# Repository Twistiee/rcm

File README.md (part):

# RCM — Relay Control Module

A CAN-controlled relay driver for a car. **21 universal channels**, each of which is
simultaneously a low-side output *and* an input — so the same board builds as a relay
controller or as a switch panel, decided in firmware rather than by a different PCB.

Designed for a [rusEFI](https://rusefi.com/) bus (uaEFI SUPER ECU + uaDASH display), but
nothing about it is rusEFI-specific beyond the choice of message IDs.

> ### A note on how this was built
>
> **This project is largely AI-developed.** The schematic, PCB layout, firmware and
> documentation were written by me working with Claude, and much of the text and code here
> came out of that. It is called out up front because some people would rather know, and
> because it should colour how much you trust it.
>
> What it does *not* mean is unreviewed or untested. The board exists and has been brought
> up on the bench; the claims in the Status section below were measured rather than
> asserted, and where something has only been reasoned about it says so. The firmware has a
> host-side unit test suite. Bring-up still found real bugs that review had missed — which
> is rather the point of the Status section.
>
> Treat it as you would any one-person hobby project: read the schematic before you build
> it, and don't put it in charge of anything you can't afford to have fail.

---

## Status — read this first

**revA has been built, powered and brought up.** Every subsystem has run on real
hardware: the MCU and its 8 MHz crystal (in use only since 2026-10-26 -- see "The core
runs from the crystal" in `firmware/README.md`), USB, the DIP straps, the EEPROM, CAN through the
transceiver onto a real bus, the IMU, the 12 V sense, the self-latching power, the
watchdog, the output drivers under a real relay load, a stored configuration surviving a
full save-reset-read cycle, and the board switching itself off. 289 host unit tests pass
alongside that.

What that does **not** mean is that it is proven in a car. Specifically, still untested:

- **board-to-board peer mirroring** — the keypad role strap is proven and a board does
  come up as a keypad, but only one board has ever been powered, so the peer link has been
  exercised only with a PC pretending to be the other board
- **more than two channels under load at once**, and nothing thermal

One genuine hardware flaw has been found, and it is a missing capability rather than a
functional fault: **revA cannot reach USB DFU.** `BOOT1` is `PB2`, which this board uses
for `SR_OE_N` and holds high at reset, so lifting BOOT0 boots from SRAM instead of the ROM
bootloader. The `J_BOOT` header is fitted and works; the pin conflict defeats it. Firmware
therefore needs an ST-Link on `J_SWD`. Configuration is unaffected — that is all over CAN.
`DESIGN.md` has the analysis and the one-net revB fix.

Bring-up found three real firmware bugs that no amount of desk testing had: a `%f` in
printf corrupting memory, a strap display that could never show a change, and a short
press on the ignition button switching the board back off. `DESIGN.md` records those and
everything else found along the way, which is a fair guide to how much is probably left.

### What happens when it resets

This is a PDM. Running a main relay, a fuel pump and an injector feed is the job, not an
edge case. But there is one behaviour to design around:

**On any reset, `R_OE` parks all 21 channels high-impedance until firmware re-enables
them.** Every channel drops. The firmware adopts `failsafe_state` and goes live as its
first act, and on revA hardware that is **22 ms**, measured by the self-test build's `W`
command rather than estimated. Add a few ms of pre-`main()` crystal and PLL startup that
`millis()` cannot see, so call it **~25 ms**. That applies equally to a cold start and to
a watchdog reset, so a main relay behind this board closes with the key rather than after
a timeout.

Most of the 22 ms is the EEPROM: the board cannot apply `failsafe_state` before it has
read `failsafe_state`, so `cfg_load()` is unavoidably inside the dropout. A scope on any
channel gives the true figure including pre-`main()` time.

So the question for each load is not "is this engine-critical" but **"what does 25 ms off
do to it?"**

| Load | 25 ms off | Verdict |
|---|---|---|
| Fan, fuel pump, lights, horn, accessories | invisible | fine |
| Injector / coil supply via a main relay | at worst a single missed event | **fine — set `failsafe_state` to hold it on** |
| **ECU power itself** | the ECU reboots, which really is a stall | **give the ECU its own ignition-switched feed** |
| **Brake lights** | harmless in itself | **hardwire anyway** — see below |

**`failsafe_state` is the board's resting state**, not just a bus-timeout behaviour: it is
what gets applied at power-up, after a watchdog reset, and whenever the bus goes quiet —
anything a CAN command has not overridden. It defaults to all-off, which is right for
lighting and wrong for anything that should be on by default. It is per-channel, so one
board can drop its lighting and hold its engine loads. Set it deliberately.

**Brake lights are a different argument.** Not dropout time — a hardwired brake switch is
simply simpler and more reliable than anything running on a microcontroller, and there is
no upside to inserting one. Wire the switch straight through, and tap the switched feed
into a spare channel set to `CH_INPUT` if you want the board to know about it. 1.2 mA, and
it cannot affect the lamps.

Roadworthiness and legal compliance of anything you build with this are yours.

---

## What it does

| | |
|---|---|
| **Channels** | 21, low-side switched, 7 per driver |
| **Drivers** | 3 × TPL7407L (MOSFET, not Darlington — see below) |
| **I/O expansion** | 74HC595 out / 74HC165 in, daisy-chained |
| **MCU** | STM32F446RET6, LQFP-64 |
| **Bus** | CAN, switchable termination, any exact bitrate |
| **Sensing** | every channel is read back continuously, including while driving |
| **IMU** | Bosch BMI270, 6-axis |
| **Board** | 140 × 70 mm, 4-layer, solid ground plane |

## Ratings

| | |
|---|---|
| Supply | 7–30 V (12 V nominal); board draws ~100 mA |
| **Per channel, one or two on** | **600 mA** sink, 30 V max |
| **Per channel, all 7 of a tile on** | **~250 mA** — limited by the driver package, not the silicon |
| All 21 channels | ~3.5 A total with typical 85 Ω relay coils |
| Ground return | **all channels share one pole on `J_PWR`**, ~8 A |
| Ambient | −20 to +70 °C |

The channels **switch relay coils, they do not carry load current** — that is the whole
architecture. `DESIGN.md` has the worked numbers, including why 600 mA is not an all-on
figure.

## The channel trick

Each channel's terminal connects to three things at once — a driver output, a permanently
connected 1M/270k sense divider, and a fitted 10k pull-down:

- **As an output** it sinks a relay coil to ground.
- **As an input** a button wired to +12V pulls it high; the pull-down gives 1.2mA of wetting
  current, enough to keep switch contacts from going oxide-flaky.
- **As a diagnostic**, because the divider never disconnects, an idle channel reads battery
  voltage through a healthy relay coil and 0V through a blown fuse. **Fuse detection falls
  out of the same wiring** — no extra parts.

Getting all three from one resistor took a few goes. A pull-*up* would have been the obvious
choice and it silently breaks fuse sensing: blown and healthy both read high, 20mV apart.

The same pull-down has a sting worth knowing: an un-driven channel is **not open**, it is
10k to ground, and it will pass ~1mA from anything pulled up to 12V. Relay coils ignore
that. Optocouplers and MOSFET gates do not — so a generic "active low" relay module wired
straight to a channel sits with its relays energised. `DESIGN.md` has the fix.

## Configuration

An 8-way DIP sets what can't be fixed over the bus once it's wrong:

| Pos | Function |
|---|---|
| 1 | CAN termination (passive, parallels a solder jumper) |
| 2 | Role — relay module or keypad |
| 3–4 | Node address |
| 5 | CAN bitrate — forces 500k, for when you configure yourself off the bus |
| 6 | Publish IMU data — only one board per car should |

Four relay modules and four keypads can share a bus. Everything else — channel modes,
bitrate, message IDs, failsafe states — lives in EEPROM and is changeable over CAN.

## Firmware

PlatformIO + STM32duino, in [`firmware/`](firmware/) — see
[`firmware/README.md`](firmware/README.md) for the detail.

- 21 channels, in or out per channel as a **software** table, changeable over CAN
- **Coil-circuit diagnosis** — blown fuse, missing relay, open coil or broken wire, all
  reported per channel, and a short-to-12V too
- **Input behaviours**: momentary, **toggle** (a momentary button driving a latching
  load), and **hold-to-arm** (true only once held, for things a knock must not arm)
- **Output behaviours**: steady, flash on a shared period so several channels stay in
  phase, single pulse, and delay-off
- CAN at **500 kbps by default and any exact bitrate you like**. Bit timing is solved at
  runtime for an 87.5% sample point; if a rate cannot be produced exactly, it refuses to
  start rather than running the bus 1% out
- Node addressing for 8 boards, CAN-loss failsafe, ignition-off shutdown, watchdog
- **Everything is configurable over CAN, and readable back over CAN** — every setting has
  a getter as well as a setter, so a tool can ask a board what it is rather than infer it
- Optional **keypad → relay peer mirroring**, so a button panel can drive a relay module
  with no ECU in the middle

```
pio run -d firmware                     build
pio run -d firmware -e selftest -t upload   bring-up console over USB-C
pio test -d firmware -e native          289 host unit tests
```

**Two bring-up paths.** A **USB-C console** needs nothing but the cable — it proves the
DIP, the EEPROM, the CAN controller via internal loopback, the IMU, and walks all 21
channels. A **PC-side CAN tool** (`firmware/tools/rcm_bench.py`, any python-can interface)
does monitoring, commanding and the same channel walk over the bus.

The unit tests compile the firmware's own source against a model of the board — the shift
register chains bit by bit, each channel's electrical behaviour, and the EEPROM including
its page-wrap misbehaviour. They exist because the shift-register byte order is the one
thing in this design that cannot be checked by reading the code back.

### rusEFI

Message IDs were checked against rusEFI's own source rather than guessed. The board sits at
base `0x300`, clear of everything rusEFI uses (`0x100`/`0x102`, `0x130`/`0x131`, `0x190`,
`0x200`–`0x20B`, OpenBLT, OBD2). The base is configurable if it clashes with something on
your loom.

[`docs/rcm.dbc`](docs/rcm.dbc) is generated from the firmware headers, so **uaDASH and
TunerStudio can render channel state, inputs and faults with no custom display code**.

**The board can drive channels from the ECU's own decisions, and ask the ECU to act.**
rusEFI broadcasts what it thinks its relays should be doing — main relay, fuel pump, both
fans, O2 heater, check-engine, rev limiter — as single bits. Any of those can be bound to
a channel, so the ECU decides and this board switches, which matters because rusEFI has
far fewer outputs than this board has channels. In the other direction, a button can send
any TunerStudio command: start/stop the engine, or one of rusEFI's Lua command counters,
which is how you get traction control, launch control or a map switch without either side
needing new firmware.

The BMI270 publishes as a **Bosch MM5.10** at `0x174`/`0x178`/`0x17C` — frames rusEFI
already decodes. Set `imuType = IMU_MM5_10` and yaw rate plus lateral, longitudinal and
vertical G appear in the ECU with nothing else to configure.

## Enclosure

[`enclosure/`](enclosure/) generates a sealed 3D-printable box and two lids — a keypad face
carrying eight 25 mm anti-vandal switches, and a blank plate for the relay-control build.
Wire entry is DEUTSCH DT, one aperture that fits 2, 3 and 4-way alike.

Like the PCB, it is generated by a script rather than modelled by hand; the `.FCStd` files
are output and are overwritten on every build.

## Building one

The schematic and PCB are **generated, not drawn**:

```
python gen_spec.py     ->  spec.json        the circuit, and the source of truth
python gen_plan.py     ->  board_plan.json  every part's physical position
tools/                                      schematic, placement, routing, export
```

Editing `rcm.kicad_sch` or `rcm.kicad_pcb` by hand gets overwritten. Change the generator.

`mfg/` holds the gerbers, BOM and CPL exactly as ordered, so you can send that folder to a
board house without running any of the above. It is set up for JLCPCB assembly: 4-layer,
leaded HASL, Standard PCBA (the BMI270's LGA-14 package requires it).

## Parts you must supply yourself

The board house builds the board. **These are not on the BOM and will not arrive with it** —
either because they do not mount to the PCB, or because no standard part fits.

### The buck module (required — the board does not power up without it)

A **Waveshare DC5-36-TO-DC3V3-5** step-down module, socketed onto `JB1`/`JB2`. It takes the
ignition-latched 12V rail down to 5V, which the on-board LDO then drops to 3V3.

**It ships set to 5V output and must stay that way.** Getting 3V3 from the module instead
needs per-unit pad rework, and forgetting it once puts 5V into a 3.3V MCU. The LDO exists
precisely so that step is never required.

Two things go with it:

| | |
|---|---|
| `JB2` (output, row of 6) | ordinary 2.54mm male header, **on the BOM** (`C37208`) |
| `JB1` (input, 4 pins) | **hand-fit** — 3.50mm pitch, no header is made at that spacing |

`JB1` needs four individual square pins. They set the module's ride height, so fit them
before anything else and get it square.

### Mating plugs for every terminal (required to connect anything)

The board carries the header halves; the screw plugs are yours to buy. `KF2EDGK-3.5-xP`,
also sold as `15EDGK-3.5`:

| Plug | LCSC | Mates with | Per board |
|---|---|---|---|
| 2P | `C440847` | `J_PWR`, `J_IGN` | 2 |
| 3P | `C440848` | `J_AUX`, `J_CAN1`, `J_CAN2` | 3 |
| 7P | `C440852` | `J_CH1`, `J_CH2`, `J_CH3` | 3 |

About $3.20 a board. Generic parts — any supplier stocks them.

> **Do not buy these into JLC's Parts Library expecting them to ship with the boards.**
> Confirmed the hard way on the 2026-08-08 order. That library is consignment stock for
> assembly runs, and JLC will only ship a part if the assembly process solders it down —
> a loose mating plug does not qualify. They will not add it to the board, and they will
> not put it in the box for a sane handling fee either. Money spent there is stuck: you
> own the parts and there is no way to take delivery of them.
>
> Buy the plugs somewhere else entirely.

### Optional

| | |
|---|---|
| `R_TJ` | 0R 0805 (`C17477`) — solder for permanent CAN termination instead of the DIP |
| Momentary buttons | for a keypad build: 8 off, positive-switched to +12V |
| USB-CAN adapter | for the PC-side tool. Get one with **slcan** firmware |

## Repository layout

```
gen_spec.py      -> spec.json         circuit definition, the source of truth
gen_plan.py      -> board_plan.json   every part's physical position
jlc_parts.json                        LCSC part per line; stamped into the schematic
tools/                                scripted-board pipeline
mfg/                                  gerbers, BOM, CPL as ordered
firmware/                             STM32 firmware, host unit tests, PC tools
enclosure/                            generated 3D-printable box and lids
docs/rcm.dbc                          CAN database, generated from the firmware headers
SPEC.md / DESIGN.md                   what was built, and why
```

## Honest notes

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
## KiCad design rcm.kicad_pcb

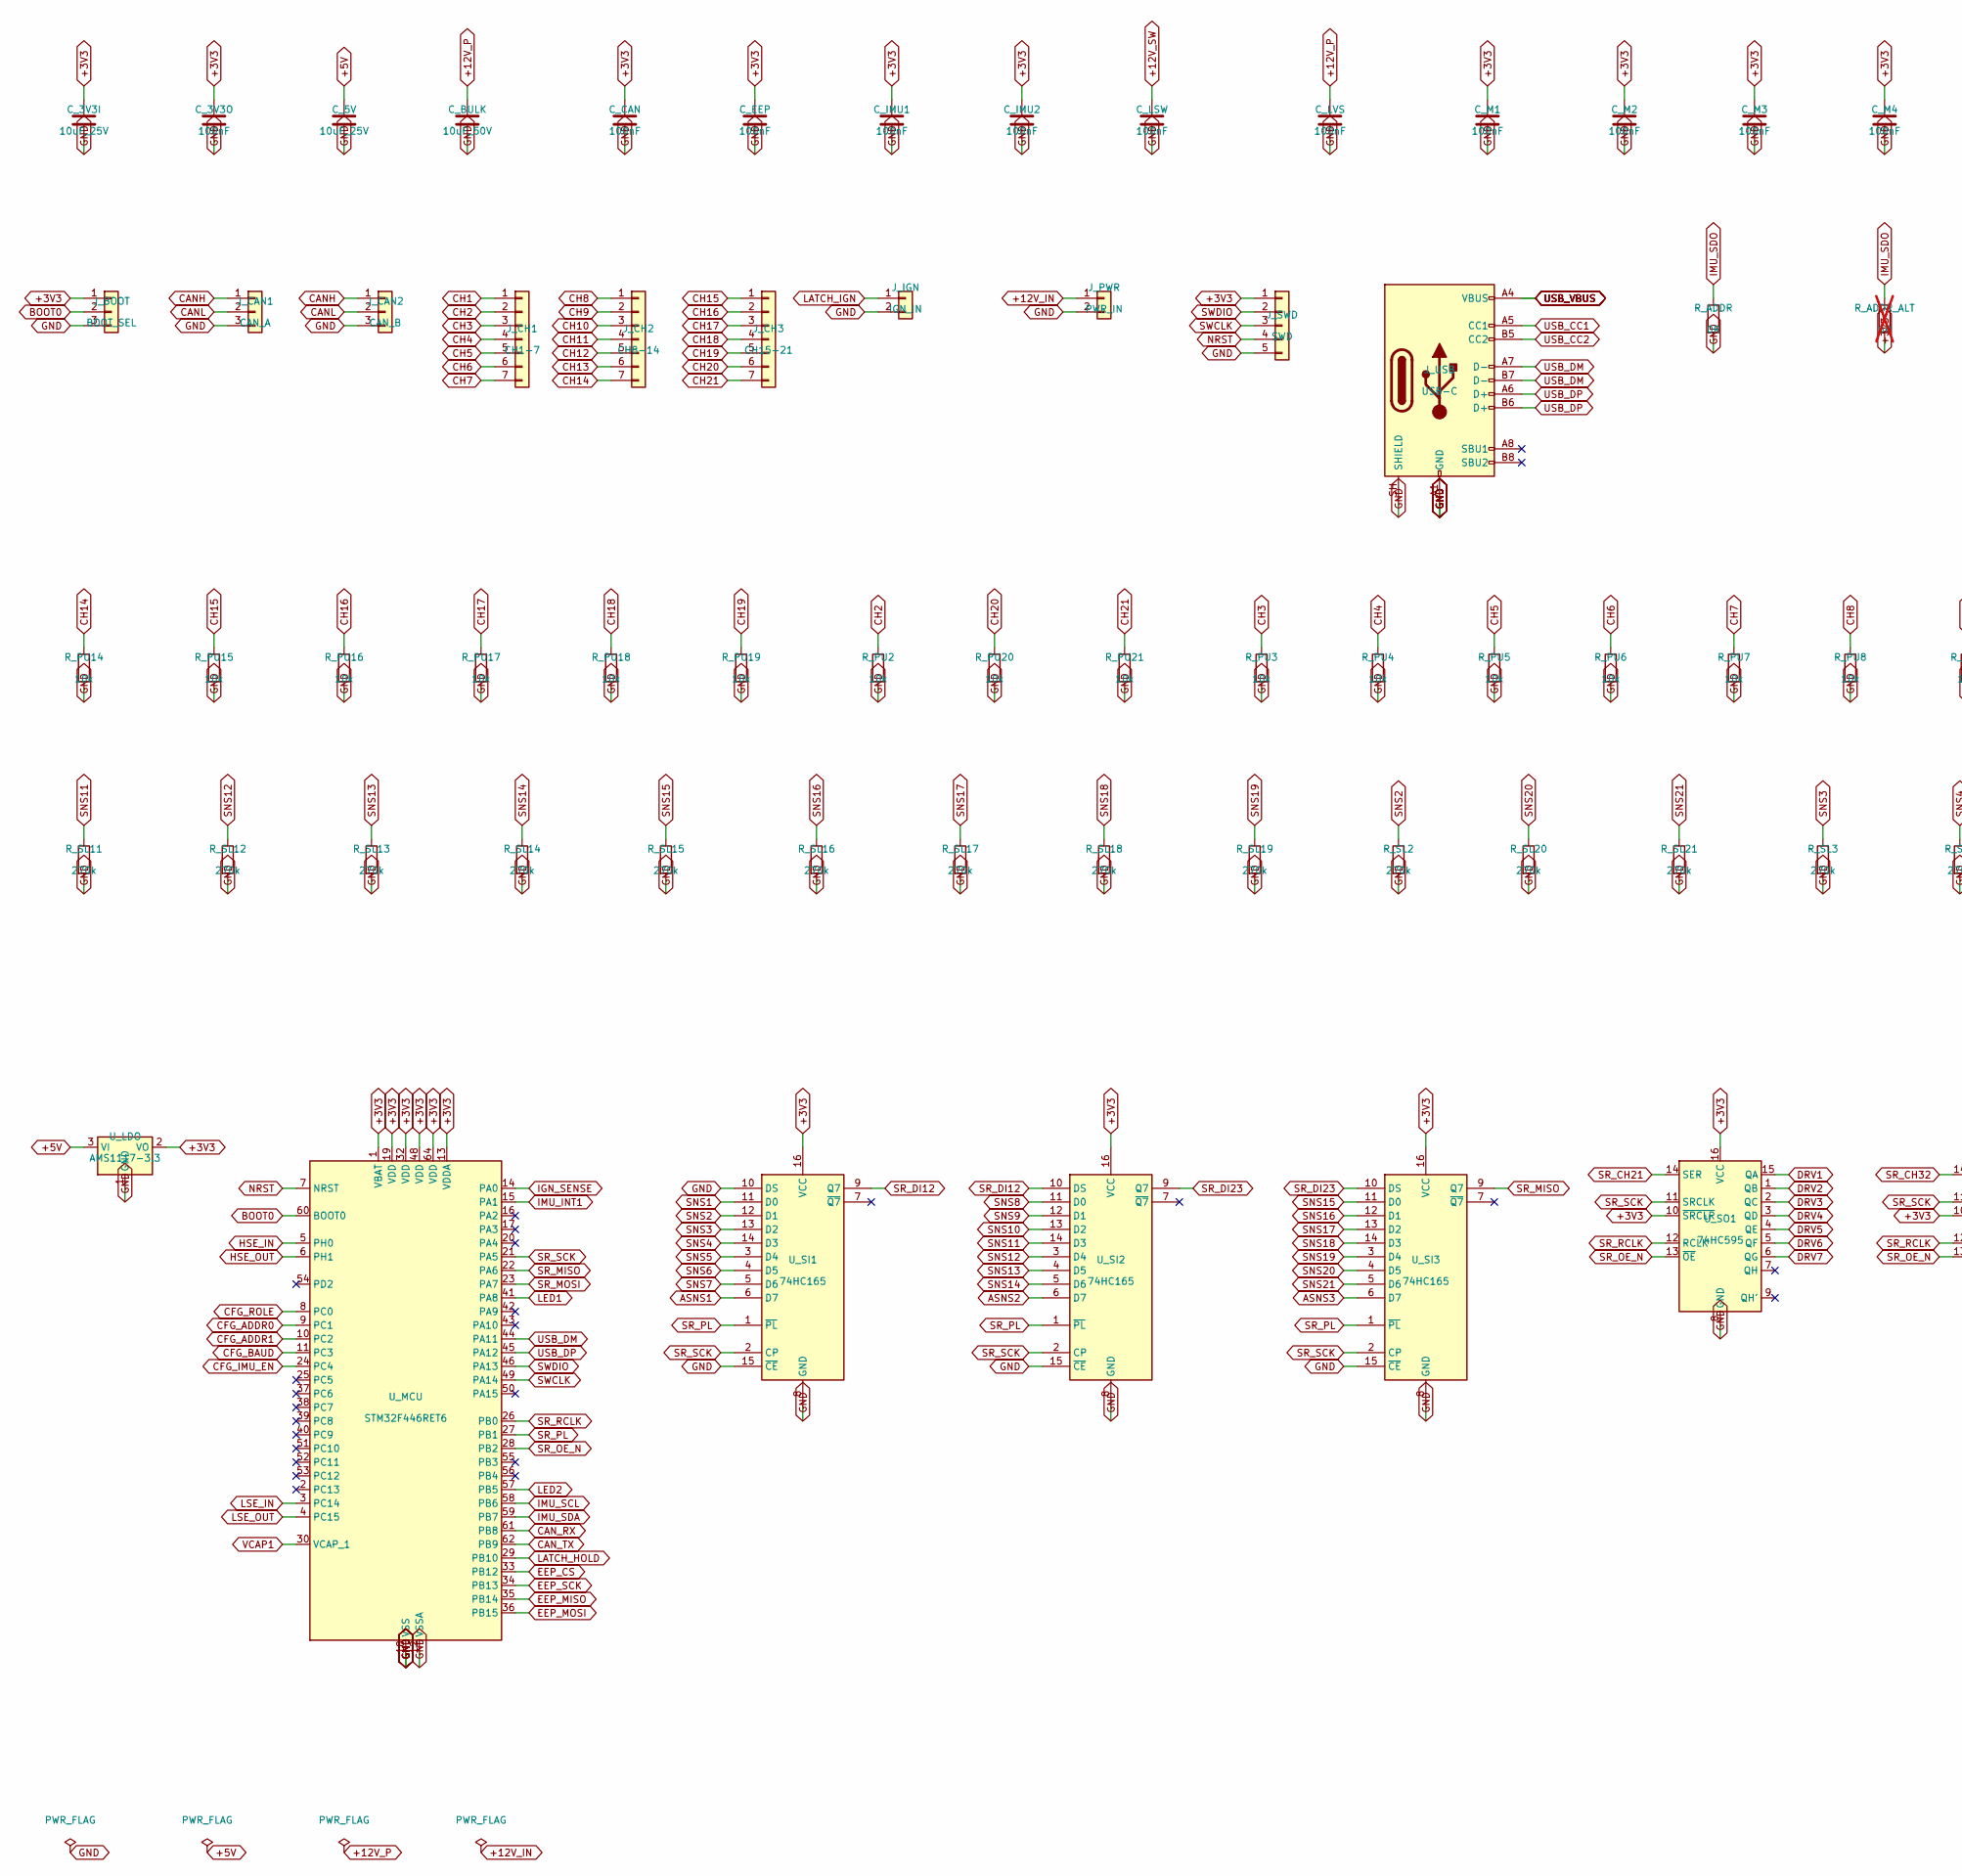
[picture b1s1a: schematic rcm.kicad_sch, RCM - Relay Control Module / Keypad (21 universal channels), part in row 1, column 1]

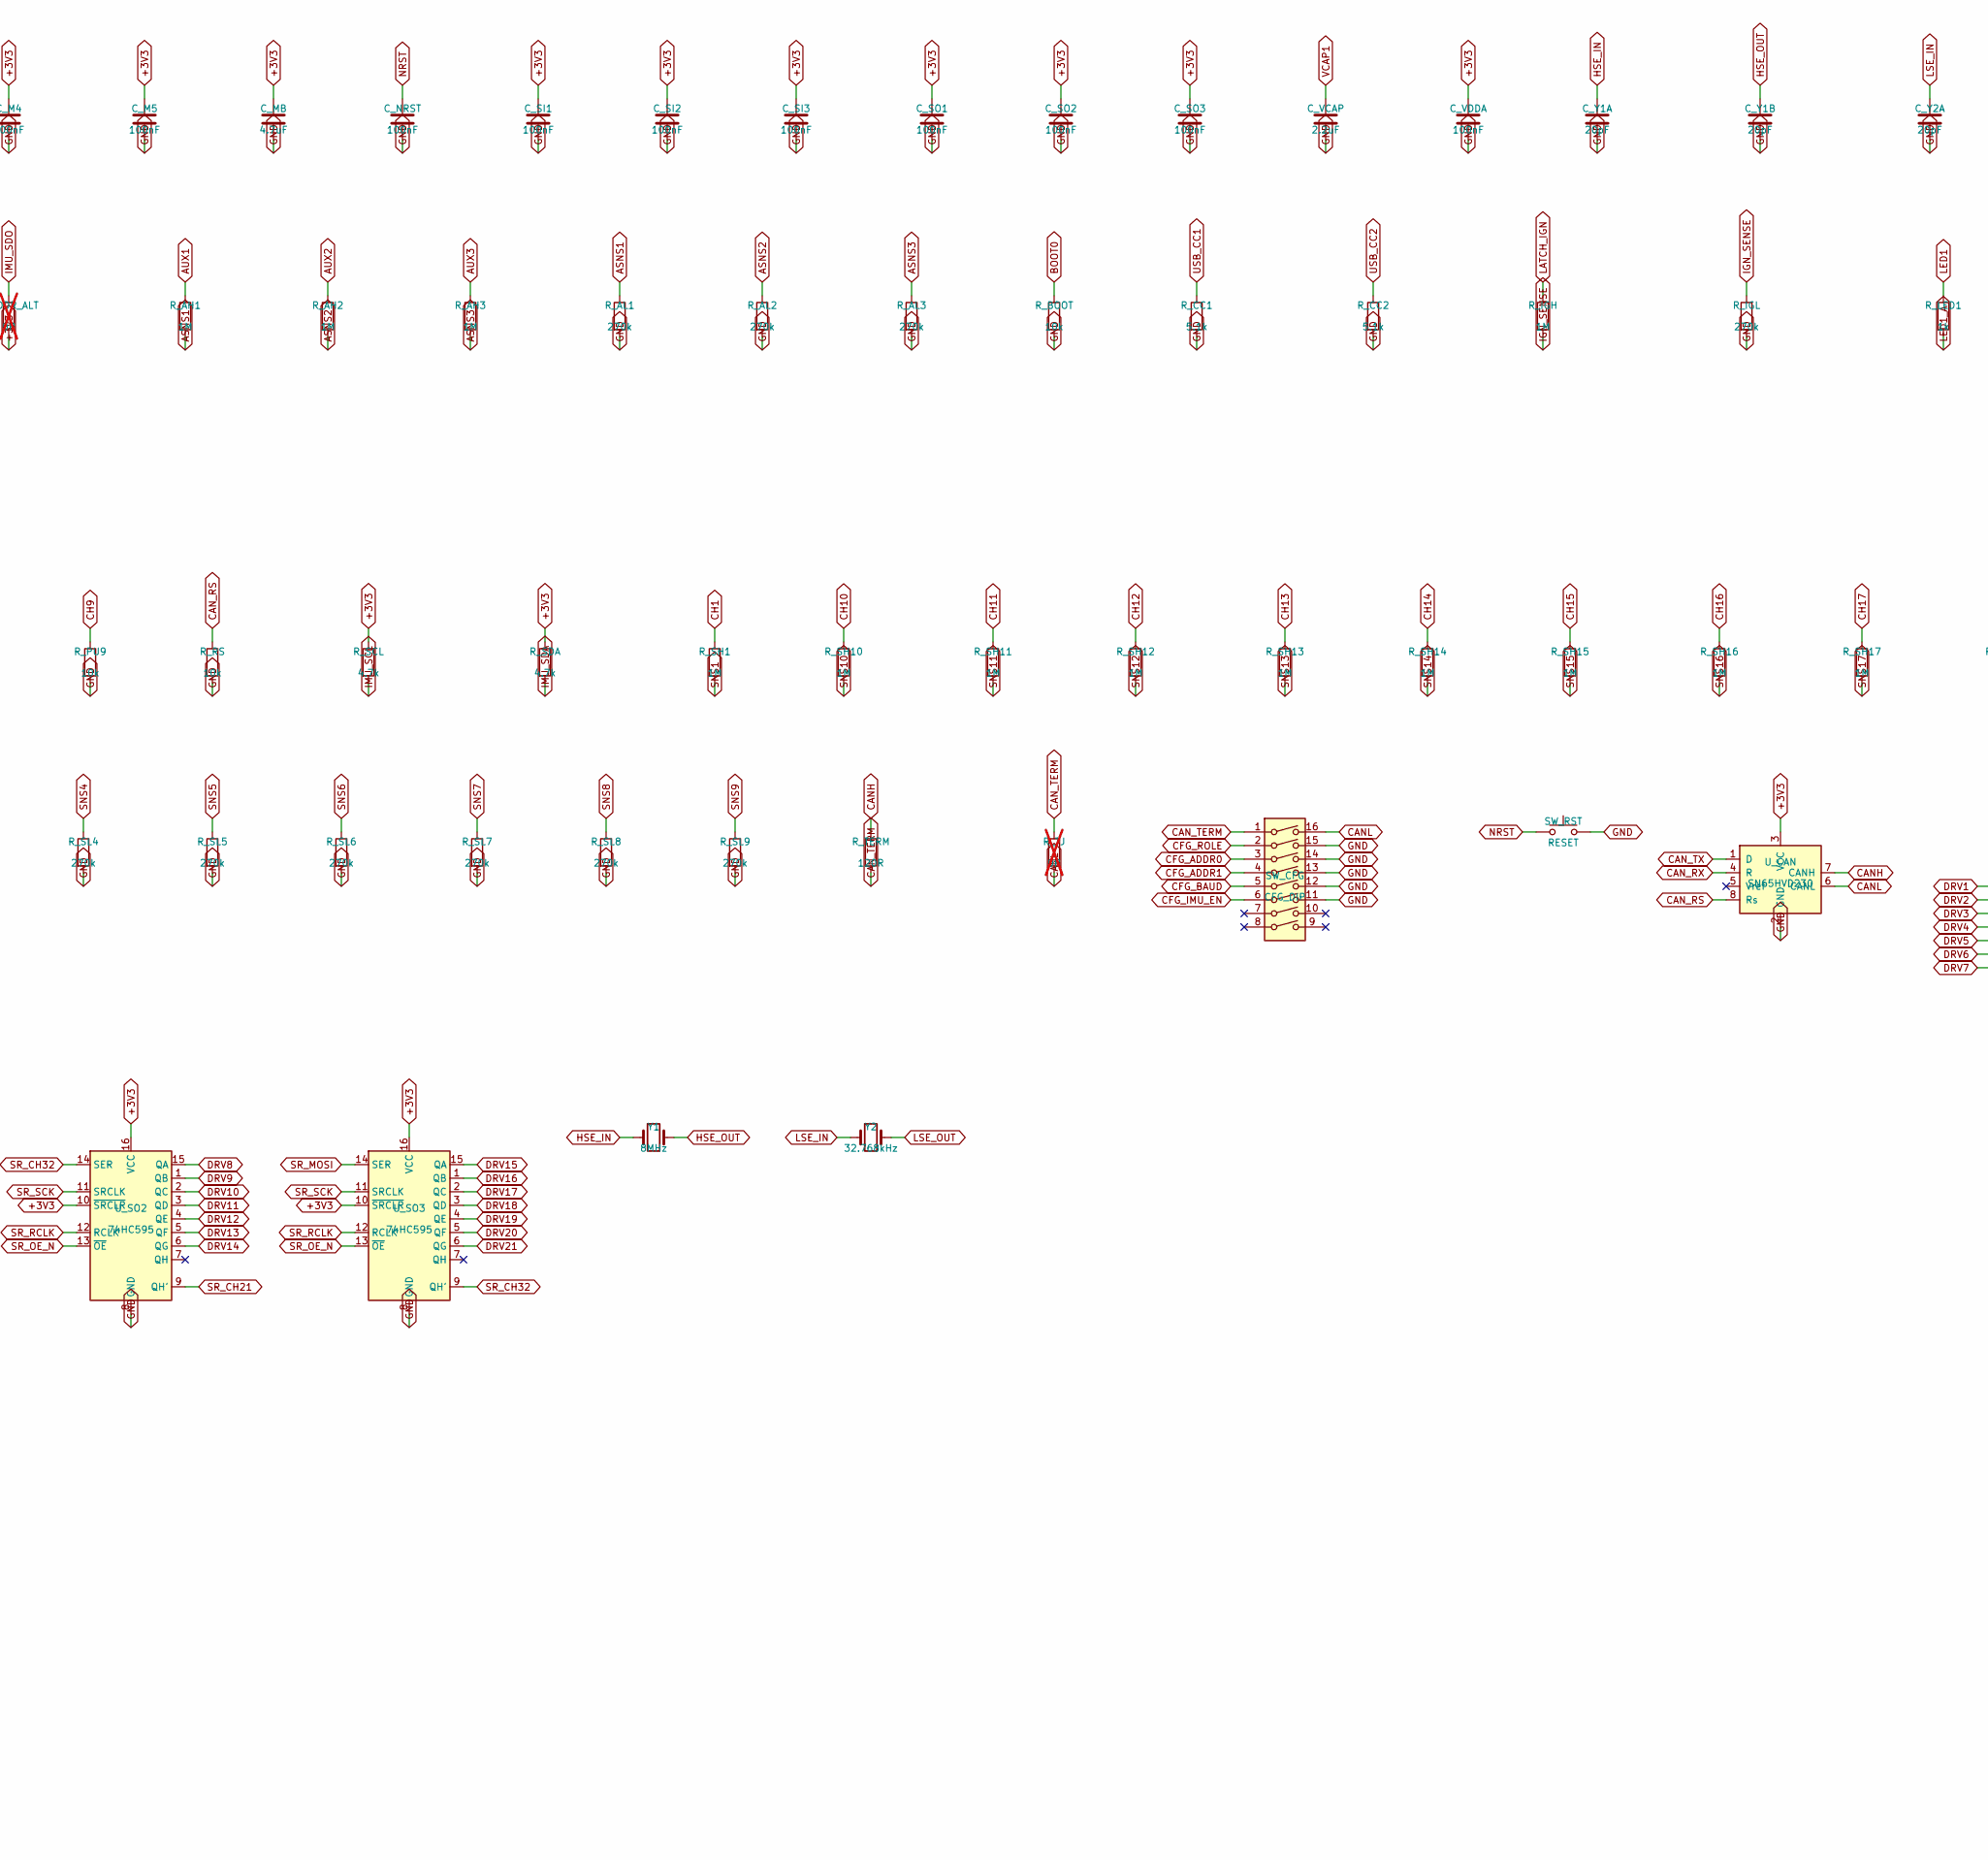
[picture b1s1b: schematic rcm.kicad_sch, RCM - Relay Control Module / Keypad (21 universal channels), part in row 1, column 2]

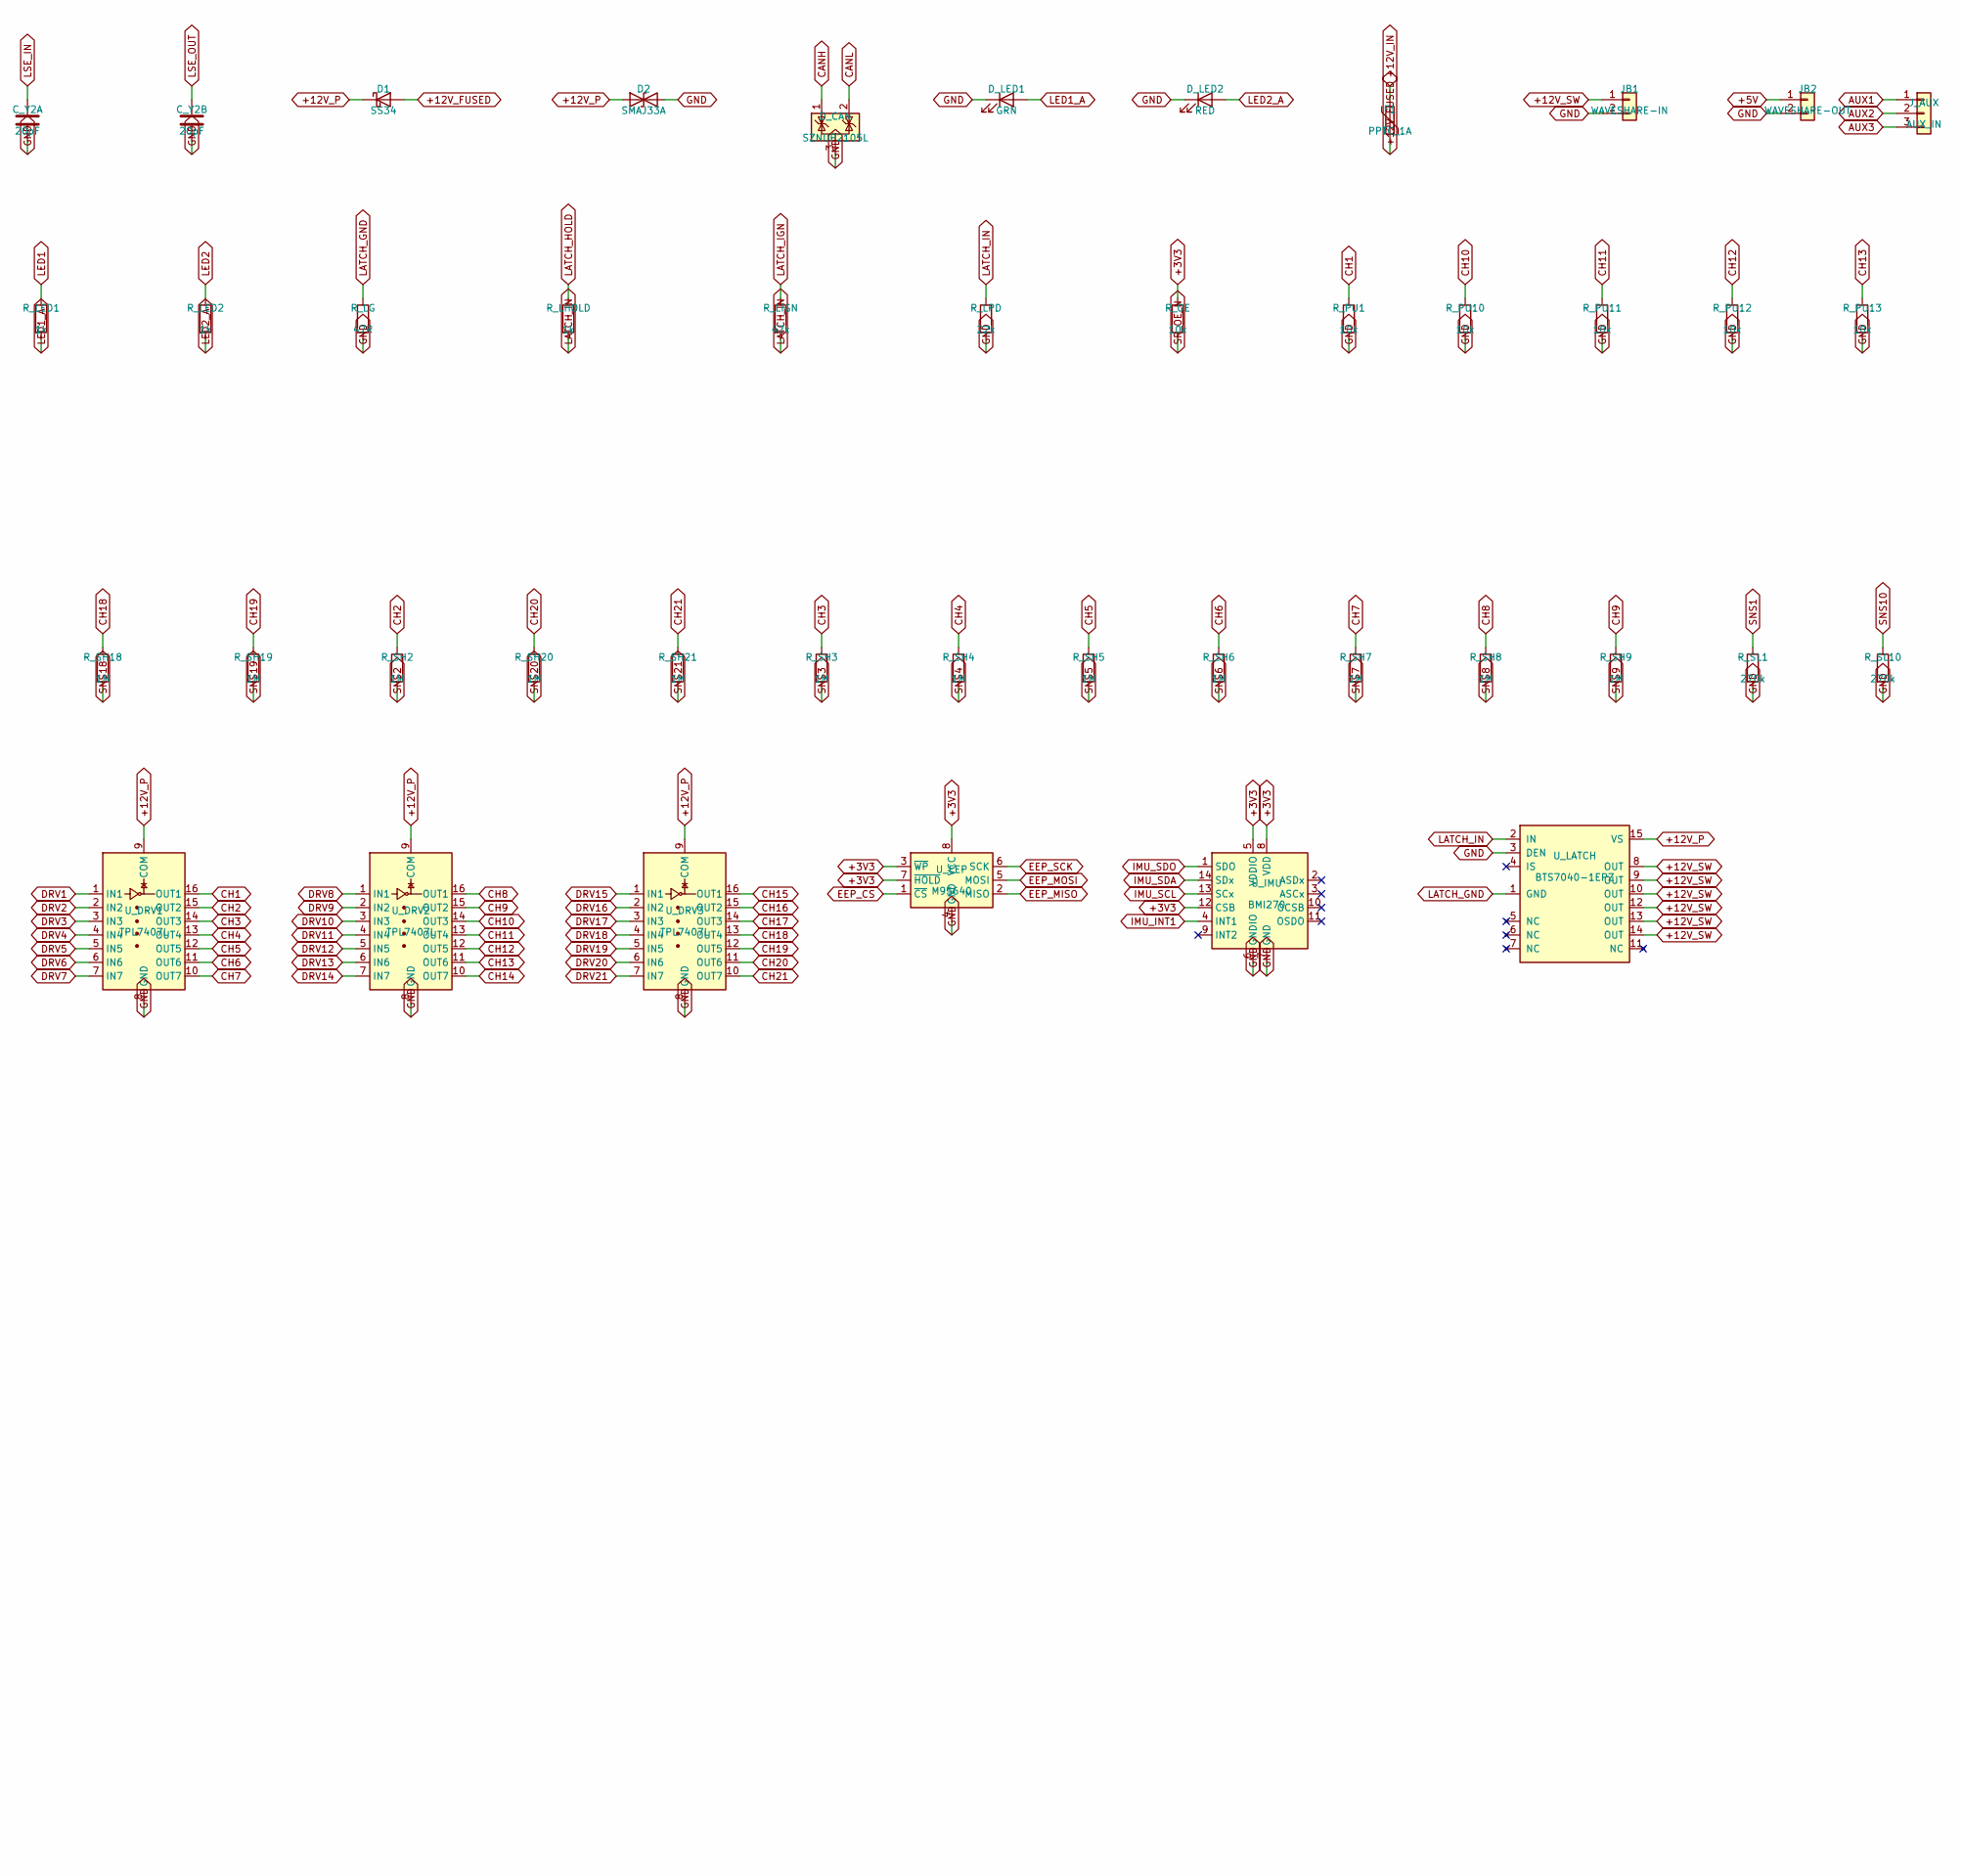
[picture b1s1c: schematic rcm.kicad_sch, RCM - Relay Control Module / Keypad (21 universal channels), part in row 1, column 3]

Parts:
C_3V3I, C_5V: 10uF_25V; C_0805_2012Metric; LCSC C15850
C_3V3O: 100nF; C_0805_2012Metric; LCSC C49678
C_BULK: 10uF_50V; C_1210_3225Metric; LCSC C2918502
C_CAN: 100nF; C_0805_2012Metric; LCSC C49678
C_EEP: 100nF; C_0805_2012Metric; LCSC C49678
C_IMU1, C_IMU2: 100nF; C_0805_2012Metric; LCSC C49678
C_LSW: 100nF; C_0805_2012Metric; LCSC C49678
C_LVS: 100nF; C_0805_2012Metric; LCSC C49678
C_M1, C_M2, C_M3, C_M4, C_M5: 100nF; C_0805_2012Metric; LCSC C49678
C_MB: 4.7uF; C_0805_2012Metric; LCSC C1779
C_NRST: 100nF; C_0805_2012Metric; LCSC C49678
C_SI1, C_SI2, C_SI3: 100nF; C_0805_2012Metric; LCSC C49678
C_SO1, C_SO2, C_SO3: 100nF; C_0805_2012Metric; LCSC C49678
C_VCAP: 2.2uF; C_0805_2012Metric; LCSC C377773
C_VDDA: 100nF; C_0805_2012Metric; LCSC C49678
C_Y1A, C_Y1B, C_Y2A, C_Y2B: 20pF; C_0805_2012Metric; LCSC C1798
D1: SS34; D_SMA; LCSC C8678
D2: SMAJ33A; D_SMA; LCSC C353454
D_CAN: SZNUP2105L; SOT-23; LCSC C233494
D_LED1: GRN; LED_0805_2012Metric; LCSC C84260
D_LED2: RED; LED_0805_2012Metric; LCSC C84256
F1: PPTC_1A; R_1812_4532Metric; LCSC C19078719
JB1: WAVESHARE-IN; WaveshareBuck_IN_2x2_P3.50mm
JB2: WAVESHARE-OUT; WaveshareBuck_OUT_3x3_P2.54mm; LCSC C37208
J_AUX: AUX_IN; TerminalBlock_KF2EDG-3.5-3P_1x03_P3.50mm_Horizontal; LCSC C441322
J_BOOT: BOOT_SEL; PinHeader_1x03_P2.54mm_Vertical; LCSC C2937625
J_CAN1: CAN_A; TerminalBlock_KF2EDG-3.5-3P_1x03_P3.50mm_Horizontal; LCSC C441322
J_CAN2: CAN_B; TerminalBlock_KF2EDG-3.5-3P_1x03_P3.50mm_Horizontal; LCSC C441322
J_CH1: CH1-7; TerminalBlock_KF2EDG-3.5-7P_1x07_P3.50mm_Horizontal; LCSC C441326
J_CH2: CH8-14; TerminalBlock_KF2EDG-3.5-7P_1x07_P3.50mm_Horizontal; LCSC C441326
J_CH3: CH15-21; TerminalBlock_KF2EDG-3.5-7P_1x07_P3.50mm_Horizontal; LCSC C441326
J_IGN: IGN_IN; TerminalBlock_KF2EDG-3.5-2P_1x02_P3.50mm_Horizontal; LCSC C441321
J_PWR: PWR_IN; TerminalBlock_KF2EDG-3.5-2P_1x02_P3.50mm_Horizontal; LCSC C441321
J_SWD: SWD; PinHeader_1x05_P2.54mm_Vertical; LCSC C492404
J_USB: USB-C; USB_C_Receptacle_HCTL_HC-TYPE-C-16P-01A; LCSC C165948
R_ADDR: 0R; R_0805_2012Metric; LCSC C17477
R_ADDR_ALT: 0R; R_0805_2012Metric; LCSC C17477; not fitted
R_AH1, R_AH2, R_AH3: 1M; R_0805_2012Metric; LCSC C17514
R_AL1, R_AL2, R_AL3: 270k; R_0805_2012Metric; LCSC C17589
R_BOOT: 10k; R_0805_2012Metric; LCSC C17414
R_CC1, R_CC2: 5.1k; R_0805_2012Metric; LCSC C27834
R_IGH: 1M; R_0805_2012Metric; LCSC C17514
R_IGL: 270k; R_0805_2012Metric; LCSC C17589
R_LED1, R_LED2: 1k; R_0805_2012Metric; LCSC C17513
R_LG: 47R; R_0805_2012Metric; LCSC C17714
R_LHOLD: 1k; R_0805_2012Metric; LCSC C17513
R_LIGN: 47k; R_0805_2012Metric; LCSC C17713
R_LPD: 22k; R_0805_2012Metric; LCSC C17560
R_OE: 10k; R_0805_2012Metric; LCSC C17414
R_PU1, R_PU2, R_PU3, R_PU4, R_PU5, R_PU6, R_PU7, R_PU8, R_PU9, R_PU10, R_PU11, R_PU12, R_PU13, R_PU14, R_PU15, R_PU16, R_PU17, R_PU18, R_PU19, R_PU20, R_PU21: 10k; R_0805_2012Metric; LCSC C17414
R_RS: 10k; R_0805_2012Metric; LCSC C17414
R_SCL: 4.7k; R_0805_2012Metric; LCSC C17673
R_SDA: 4.7k; R_0805_2012Metric; LCSC C17673
R_SH1, R_SH2, R_SH3, R_SH4, R_SH5, R_SH6, R_SH7, R_SH8, R_SH9, R_SH10, R_SH11, R_SH12, R_SH13, R_SH14, R_SH15, R_SH16, R_SH17, R_SH18, R_SH19, R_SH20, R_SH21: 1M; R_0805_2012Metric; LCSC C17514
R_SL1, R_SL2, R_SL3, R_SL4, R_SL5, R_SL6, R_SL7, R_SL8, R_SL9, R_SL10, R_SL11, R_SL12, R_SL13, R_SL14, R_SL15, R_SL16, R_SL17, R_SL18, R_SL19, R_SL20, R_SL21: 270k; R_0805_2012Metric; LCSC C17589
R_TERM: 120R; R_0805_2012Metric; LCSC C17437
R_TJ: 0R; R_0805_2012Metric; LCSC C17477; not fitted
SW_CFG: CFG_DIP; SW_DIP_SPSTx08_Slide_KingTek_DSHP08TS_W7.62mm_P1.27mm; LCSC C6386921
SW_RST: RESET; SW_SPST_TL3342; LCSC C2886894
U_CAN: SN65HVD230; SOIC-8_3.9x4.9mm_P1.27mm; LCSC C12084
U_DRV1, U_DRV2, U_DRV3: TPL7407L; TSSOP-16_4.4x5mm_P0.65mm; LCSC C2149827
U_EEP: M95640; SOIC-8_3.9x4.9mm_P1.27mm; LCSC C283461
U_IMU: BMI270; Bosch_LGA-14_3x2.5mm_P0.5mm; LCSC C2836813
U_LATCH: BTS7040-1EPZ; Infineon_PG-TSDSO-14-22; LCSC C534838
U_LDO: AMS1117-3.3; SOT-223-3_TabPin2; LCSC C6186
U_MCU: STM32F446RET6; LQFP-64_10x10mm_P0.5mm; LCSC C69336
U_SI1, U_SI2, U_SI3: 74HC165; SOIC-16_3.9x9.9mm_P1.27mm; LCSC C22384789
U_SO1, U_SO2, U_SO3: 74HC595; SOIC-16_3.9x9.9mm_P1.27mm; LCSC C5947
Y1: 8MHz; Crystal_SMD_5032-2Pin_5.0x3.2mm; LCSC C115962
Y2: 32.768kHz; Crystal_SMD_3215-2Pin_3.2x1.5mm; LCSC C32346

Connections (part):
+3V3: C_3V3I.1, C_3V3O.1, C_CAN.1, C_EEP.1, C_IMU1.1, C_IMU2.1, C_M1.1, C_M2.1, C_M3.1, C_M4.1, C_M5.1, C_MB.1, C_SI1.1, C_SI2.1, C_SI3.1, C_SO1.1, C_SO2.1, C_SO3.1, C_VDDA.1, J_BOOT.1, J_SWD.1, R_ADDR_ALT.2, R_OE.1, R_SCL.1, R_SDA.1, U_CAN.3 (VCC), U_EEP.3 (~WP), U_EEP.7 (~HOLD), U_EEP.8 (VCC), U_IMU.5 (VDDIO), U_IMU.8 (VDD), U_IMU.12 (CSB), U_LDO.2 (VO), U_MCU.1 (VBAT), U_MCU.13 (VDDA), U_MCU.19 (VDD), U_MCU.32 (VDD), U_MCU.48 (VDD), U_MCU.64 (VDD), U_SI1.16 (VCC), U_SI2.16 (VCC), U_SI3.16 (VCC), U_SO1.10 (~SRCLR), U_SO1.16 (VCC), U_SO2.10 (~SRCLR), U_SO2.16 (VCC), U_SO3.10 (~SRCLR), U_SO3.16 (VCC)
+5V: C_5V.1, JB2.1, U_LDO.3 (VI)
+12V_FUSED: D1.2 (A), F1.2
+12V_IN: F1.1, J_PWR.1
+12V_P: C_BULK.1, C_LVS.1, D1.1 (K), D2.1 (A1), U_DRV1.9 (COM), U_DRV2.9 (COM), U_DRV3.9 (COM), U_LATCH.15 (VS)
+12V_SW: C_LSW.1, JB1.1, U_LATCH.8 (OUT), U_LATCH.9 (OUT), U_LATCH.10 (OUT), U_LATCH.12 (OUT), U_LATCH.13 (OUT), U_LATCH.14 (OUT)
ASNS1: R_AH1.2, R_AL1.1, U_SI1.6 (D7)
ASNS2: R_AH2.2, R_AL2.1, U_SI2.6 (D7)
ASNS3: R_AH3.2, R_AL3.1, U_SI3.6 (D7)
AUX1: J_AUX.1, R_AH1.1
AUX2: J_AUX.2, R_AH2.1
AUX3: J_AUX.3, R_AH3.1
BOOT0: J_BOOT.2, R_BOOT.1, U_MCU.60 (BOOT0)
CANH: D_CAN.1 (K), J_CAN1.1, J_CAN2.1, R_TERM.1, U_CAN.7 (CANH)
CANL: D_CAN.2 (K), J_CAN1.2, J_CAN2.2, R_TJ.2, SW_CFG.16, U_CAN.6 (CANL)
CAN_RS: R_RS.1, U_CAN.8 (Rs)
CAN_RX: U_CAN.4 (R), U_MCU.61 (PB8)
CAN_TERM: R_TERM.2, R_TJ.1, SW_CFG.1
CAN_TX: U_CAN.1 (D), U_MCU.62 (PB9)
CFG_ADDR0: SW_CFG.3, U_MCU.9 (PC1)
CFG_ADDR1: SW_CFG.4, U_MCU.10 (PC2)
CFG_BAUD: SW_CFG.5, U_MCU.11 (PC3)
CFG_IMU_EN: SW_CFG.6, U_MCU.24 (PC4)
CFG_ROLE: SW_CFG.2, U_MCU.8 (PC0)
CH1: J_CH1.1, R_PU1.1, R_SH1.1, U_DRV1.16 (OUT1)
CH2: J_CH1.2, R_PU2.1, R_SH2.1, U_DRV1.15 (OUT2)
CH3: J_CH1.3, R_PU3.1, R_SH3.1, U_DRV1.14 (OUT3)
CH4: J_CH1.4, R_PU4.1, R_SH4.1, U_DRV1.13 (OUT4)
CH5: J_CH1.5, R_PU5.1, R_SH5.1, U_DRV1.12 (OUT5)
CH6: J_CH1.6, R_PU6.1, R_SH6.1, U_DRV1.11 (OUT6)
CH7: J_CH1.7, R_PU7.1, R_SH7.1, U_DRV1.10 (OUT7)
CH8: J_CH2.1, R_PU8.1, R_SH8.1, U_DRV2.16 (OUT1)
CH9: J_CH2.2, R_PU9.1, R_SH9.1, U_DRV2.15 (OUT2)
CH10: J_CH2.3, R_PU10.1, R_SH10.1, U_DRV2.14 (OUT3)
CH11: J_CH2.4, R_PU11.1, R_SH11.1, U_DRV2.13 (OUT4)
CH12: J_CH2.5, R_PU12.1, R_SH12.1, U_DRV2.12 (OUT5)
CH13: J_CH2.6, R_PU13.1, R_SH13.1, U_DRV2.11 (OUT6)
CH14: J_CH2.7, R_PU14.1, R_SH14.1, U_DRV2.10 (OUT7)
CH15: J_CH3.1, R_PU15.1, R_SH15.1, U_DRV3.16 (OUT1)
CH16: J_CH3.2, R_PU16.1, R_SH16.1, U_DRV3.15 (OUT2)
CH17: J_CH3.3, R_PU17.1, R_SH17.1, U_DRV3.14 (OUT3)
CH18: J_CH3.4, R_PU18.1, R_SH18.1, U_DRV3.13 (OUT4)
CH19: J_CH3.5, R_PU19.1, R_SH19.1, U_DRV3.12 (OUT5)
CH20: J_CH3.6, R_PU20.1, R_SH20.1, U_DRV3.11 (OUT6)
CH21: J_CH3.7, R_PU21.1, R_SH21.1, U_DRV3.10 (OUT7)
DRV1: U_DRV1.1 (IN1), U_SO1.15 (QA)
DRV2: U_DRV1.2 (IN2), U_SO1.1 (QB)
DRV3: U_DRV1.3 (IN3), U_SO1.2 (QC)
DRV4: U_DRV1.4 (IN4), U_SO1.3 (QD)
DRV5: U_DRV1.5 (IN5), U_SO1.4 (QE)
DRV6: U_DRV1.6 (IN6), U_SO1.5 (QF)
DRV7: U_DRV1.7 (IN7), U_SO1.6 (QG)
DRV8: U_DRV2.1 (IN1), U_SO2.15 (QA)
DRV9: U_DRV2.2 (IN2), U_SO2.1 (QB)
DRV10: U_DRV2.3 (IN3), U_SO2.2 (QC)
DRV11: U_DRV2.4 (IN4), U_SO2.3 (QD)
DRV12: U_DRV2.5 (IN5), U_SO2.4 (QE)
DRV13: U_DRV2.6 (IN6), U_SO2.5 (QF)
DRV14: U_DRV2.7 (IN7), U_SO2.6 (QG)
DRV15: U_DRV3.1 (IN1), U_SO3.15 (QA)
DRV16: U_DRV3.2 (IN2), U_SO3.1 (QB)
DRV17: U_DRV3.3 (IN3), U_SO3.2 (QC)
DRV18: U_DRV3.4 (IN4), U_SO3.3 (QD)
DRV19: U_DRV3.5 (IN5), U_SO3.4 (QE)
DRV20: U_DRV3.6 (IN6), U_SO3.5 (QF)
DRV21: U_DRV3.7 (IN7), U_SO3.6 (QG)
EEP_CS: U_EEP.1 (~CS), U_MCU.33 (PB12)
EEP_MISO: U_EEP.2 (MISO), U_MCU.35 (PB14)
EEP_MOSI: U_EEP.5 (MOSI), U_MCU.36 (PB15)
EEP_SCK: U_EEP.6 (SCK), U_MCU.34 (PB13)
GND: C_3V3I.2, C_3V3O.2, C_5V.2, C_BULK.2, C_CAN.2, C_EEP.2, C_IMU1.2, C_IMU2.2, C_LSW.2, C_LVS.2, C_M1.2, C_M2.2, C_M3.2, C_M4.2, C_M5.2, C_MB.2, C_NRST.2, C_SI1.2, C_SI2.2, C_SI3.2, C_SO1.2, C_SO2.2, C_SO3.2, C_VCAP.2, C_VDDA.2, C_Y1A.2, C_Y1B.2, C_Y2A.2, C_Y2B.2, D2.2 (A2), D_CAN.3 (A), D_LED1.1 (K), D_LED2.1 (K), JB1.2, JB2.2, J_BOOT.3, J_CAN1.3, J_CAN2.3, J_IGN.2, J_PWR.2, J_SWD.5, J_USB.A1 (GND), J_USB.A12 (GND), J_USB.B1 (GND), J_USB.B12 (GND), J_USB.SH (SHIELD), R_ADDR.2, R_AL1.2, R_AL2.2, R_AL3.2, R_BOOT.2, R_CC1.2, R_CC2.2, R_IGL.2, R_LG.2, R_LPD.2, R_PU1.2, R_PU2.2, R_PU3.2, R_PU4.2, R_PU5.2, R_PU6.2, R_PU7.2, R_PU8.2, R_PU9.2, R_PU10.2, R_PU11.2, R_PU12.2, R_PU13.2, R_PU14.2, R_PU15.2, R_PU16.2, R_PU17.2, R_PU18.2, R_PU19.2, R_PU20.2, R_PU21.2, R_RS.2, R_SL1.2, R_SL2.2, R_SL3.2, R_SL4.2, R_SL5.2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
HSE_IN: C_Y1A.1, U_MCU.5 (PH0), Y1.1
HSE_OUT: C_Y1B.1, U_MCU.6 (PH1), Y1.2
IGN_SENSE: R_IGH.2, R_IGL.1, U_MCU.14 (PA0)
IMU_INT1: U_IMU.4 (INT1), U_MCU.15 (PA1)
IMU_SCL: R_SCL.2, U_IMU.13 (SCx), U_MCU.58 (PB6)
IMU_SDA: R_SDA.2, U_IMU.14 (SDx), U_MCU.59 (PB7)
IMU_SDO: R_ADDR.1, R_ADDR_ALT.1, U_IMU.1 (SDO)
LATCH_GND: R_LG.1, U_LATCH.1 (GND)
LATCH_HOLD: R_LHOLD.1, U_MCU.29 (PB10)
LATCH_IGN: J_IGN.1, R_IGH.1, R_LIGN.1
LATCH_IN: R_LHOLD.2, R_LIGN.2, R_LPD.1, U_LATCH.2 (IN)
LED1: R_LED1.1, U_MCU.41 (PA8)
LED1_A: D_LED1.2 (A), R_LED1.2
LED2: R_LED2.1, U_MCU.57 (PB5)
LED2_A: D_LED2.2 (A), R_LED2.2
LSE_IN: C_Y2A.1, U_MCU.3 (PC14), Y2.1
LSE_OUT: C_Y2B.1, U_MCU.4 (PC15), Y2.2
NRST: C_NRST.1, J_SWD.4, SW_RST.1, U_MCU.7 (NRST)
SNS1: R_SH1.2, R_SL1.1, U_SI1.11 (D0)
SNS2: R_SH2.2, R_SL2.1, U_SI1.12 (D1)
SNS3: R_SH3.2, R_SL3.1, U_SI1.13 (D2)
SNS4: R_SH4.2, R_SL4.1, U_SI1.14 (D3)
SNS5: R_SH5.2, R_SL5.1, U_SI1.3 (D4)
SNS6: R_SH6.2, R_SL6.1, U_SI1.4 (D5)
SNS7: R_SH7.2, R_SL7.1, U_SI1.5 (D6)
SNS8: R_SH8.2, R_SL8.1, U_SI2.11 (D0)
SNS9: R_SH9.2, R_SL9.1, U_SI2.12 (D1)
SNS10: R_SH10.2, R_SL10.1, U_SI2.13 (D2)
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
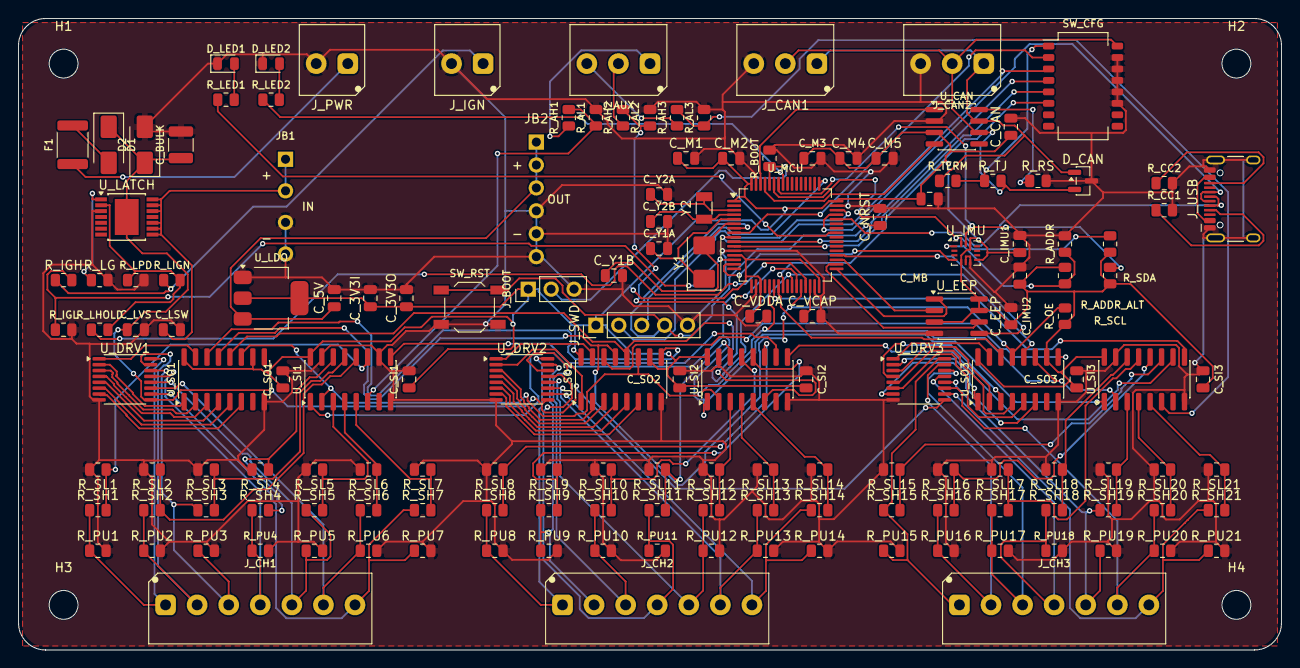
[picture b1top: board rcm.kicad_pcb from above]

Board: 2 copper layers, 140.0 x 70.0 mm, 159 parts (0 on the bottom side), 128 nets.

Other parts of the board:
H1, H2, H3, H4: MountingHole_3.2mm_M3

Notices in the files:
README.md:
Licence:
[MIT](LICENSE) — hardware design files included. Copy it, change it, sell it, no
attribution burden beyond keeping the notice.
MIT rather than a public-domain dedication for one reason: the **"AS IS, WITHOUT WARRANTY"
clause. This switches vehicle electrics, and that paragraph is worth keeping.
Bosch's vendored BMI270 driver is separately licensed under BSD-3-Clause.
